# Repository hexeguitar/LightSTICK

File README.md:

# LightStick

![alt text][pic1]

## Features:  
- High CRI >95 dual color white leds (cold/warm).
- Modular system with one Master module and up to 4 secondary modules.
- Linear constant current LED drivers.
- IR remote control (brightness, color, presets).
- Optional analog control using potentiometers (not implemented yet).
- Power saving OFF mode.
- Current consumption: about 300mA per module in full brightness.
  
## Background/design:
Traditional and common studio lights used in photography and filming usually use a high current PWM to control the brightness. For my use in filming analog instruments and effects (often high gain ones) i really needed something quiet and as noise/EMI free as possible.  
That's how the **LightSTICK** modular light was born - it uses linear constant current drivers for the LEDs and a DC control voltage to set the brightness and the color temperature.  
## Modularity
The design is modular, one "Master" module, consisting the MCU and IR receiver can control up to 4 additional secondary modules connected via a 5 wire bus:  
* 12V supply for the LEDs
* 5V supply for the constant current drivers / control voltage reference
* **WH** - cold white control voltage
* **WWH** - warm white control voltage
* GND  
## LED type  
LEDs used in the LightSTICK are manufactured by the LEDGUON company, obtainable through their direct store at Aliexpress.  
The part number is: **JH-5054WWW12S35-T8A-97**
![alt text][pic2]  

## PCB design
PCB is designed as 4 layer one, using the most of the top layer for heat dissipation.  
![alt text][pic3]  
## Firmware
LightSTICK uses ATtiny806 as it's MCU. The firmware is available as Platformio project and compiled with Arduino framework. Only one library is required and included in the /lib folder: **Arduino-IRremote**, which has been modified to support the ATtiny806 chip.  

### Pot support
Initially i planned to use two potentiometers as control input for the brightness and color temp. However, during the firmware development the IR remote control turned out to be much more useful, hence i went that route. Nevertheless, the footprint for pots are provided and a basic interrupt driven ADC read functionality is implemented in case some would need it. Expanding the firmware should not be a hard task.  

### IR remote control
The easiest way to adapt an existing tv/camera remote as LightSTICK controller is to analyze it using a generic arduino board and one of the examples from the **Arduino-IRremote** library (ie. "Receive Demo). Simply write down the protocol of the remote and all the command codes for each button. In my case of a small remote from an old TC card the results were as follows:  
```
Protocol:           RC5

...
+:                  Command=0x3 Toggle=1 Raw-Data=0x19C3
                    Command=0x3 Raw-Data=0x11C3

-:                  Command=0x9 Toggle=1 Raw-Data=0x19C9
                    Command=0x9 Raw-Data=0x11C9

Up:                 Command=0x6 Toggle=1 Raw-Data=0x19C6
                    Command=0x6 Raw-Data=0x11C6
                    
Down:               Command=0xC Toggle=1 Raw-Data=0x19CC
                    Command=0xC Raw-Data=0x11CC

1:                  Command=0xF Toggle=1 Raw-Data=0x19CF
                    Command=0xF Raw-Data=0x11CF

2:                  Command=0x15 Raw-Data=0x11D5
                    Command=0x15 Toggle=1 Raw-Data=0x19D5

3:                  Command=0x10 Toggle=1 Raw-Data=0x19D0
                    Command=0x10 Raw-Data=0x11D0

4:                  Command=0x18 Raw-Data=0x11D8
                    Command=0x18 Toggle=1 Raw-Data=0x19D8

5:                  Command=0x1B Toggle=1 Raw-Data=0x19DB
                    Command=0x1B Raw-Data=0x11DB
...
```
The command codes are then used in the IR command table (*`remote.h`* file)
```c++
/**
 * @brief IR remote command table. 
 * 
 */
typedef enum
{
    CMD_IDLE            = 0x00,
    CMD_PWR_TGL         = 0x39,     // key POWER
    CMD_BRIGHT_INC      = 0x03,     // key +
    CMD_BRIGHT_DEC      = 0x09,     // key -
    CMD_BRIGHT_MAX      = 0x30,     // key PLAY
    CMD_COLOR_WARMER    = 0x06,     // key UP
    CMD_COLOR_COLDER    = 0x0C,     // key DOWN
    CMD_COLOR_WARM      = 0x33,     // key FWD
    CMD_COLOR_COLD      = 0x2D,     // key REW
    CMD_PRESET_0        = 0x27,     // key 0
    CMD_PRESET_1        = 0x0F,     // key 1
    CMD_PRESET_2        = 0x15,     // key 2
    CMD_PRESET_3        = 0x10,     // key 3
    CMD_PRESET_4        = 0x18,     // key 4
    CMD_PRESET_5        = 0x1B,     // key 5
    CMD_PRESET_6        = 0x1E,     // key 6
    CMD_PRESET_7        = 0x11,     // key 7
    CMD_PRESET_8        = 0x21,     // key 8
    CMD_PRESET_9        = 0x12,     // key 9
    CMD_RESET_MCU       = 0x3C,     // key STOP
    CMD_STORE_PRESET    = 0x36      // key REC
}ir_cmd_t;
```  
![alt text][pic5]  
### Low power design  
Both, the electronics and the firmware implements low power design techniques making the LightSTICK useful as battery operated device, too.  
In **OFF** state the global 12V and 5V power busses are disabled, the MCU is in power off state, practically leaving the IR receiver as a single powered on device.

### Programming
ATtiny806 uses UPDI protocol for programming the flash. The programmer should be connected to the pads marked !UPDI, 5V and GND, depending on the used device. Programmers like the Atmel-ICE require the 5V VDD to set the proper logic level.  
An UPDI programmer can be also made of a generic Arduino board. In that case make sure the board runs on 5V, only the UPDI and GND connections will be required.  
The `platformio.ini` file assumes the Atmel-ICE programmer. This file has to be modified if another type of programmer is used.      
First use the following command in Platformio to set the correct fuse values:  
```
pio run -t fuses -e set_fuses
```
and then normally upload the firmware.  

## Applications  
Cheap "book lamp" rebuilt into remote controlled high CRI light for macro photography. Improved thermals by mounting the pcbs on two pieces of 15mm wide alu flat profile with 3mm thick silicon pad isolation.
![alt text][pic6]  
A ring of 5 LightSTICKs used as source of indirect light in macro photography.
![alt text][pic7]  
![alt text][pic4]  

----  
Copyright 2021 by Piotr Zapart  
www.hexefx.com

[pic1]: pics/LighSTICK_a.png "LightSTICK main"
[pic2]: pics/Led_type.jpg "LEDs used in the project"
[pic3]: pics/LightStick9.jpg "LightSTICK"
[pic4]: pics/LightStick8.jpg "LightSTICK"
[pic5]: pics/LightStick6.jpg "LightSTICK"
[pic6]: pics/LightStick11.jpg "LightSTICK"
[pic7]: pics/LightStick12.jpg "LightSTICK"

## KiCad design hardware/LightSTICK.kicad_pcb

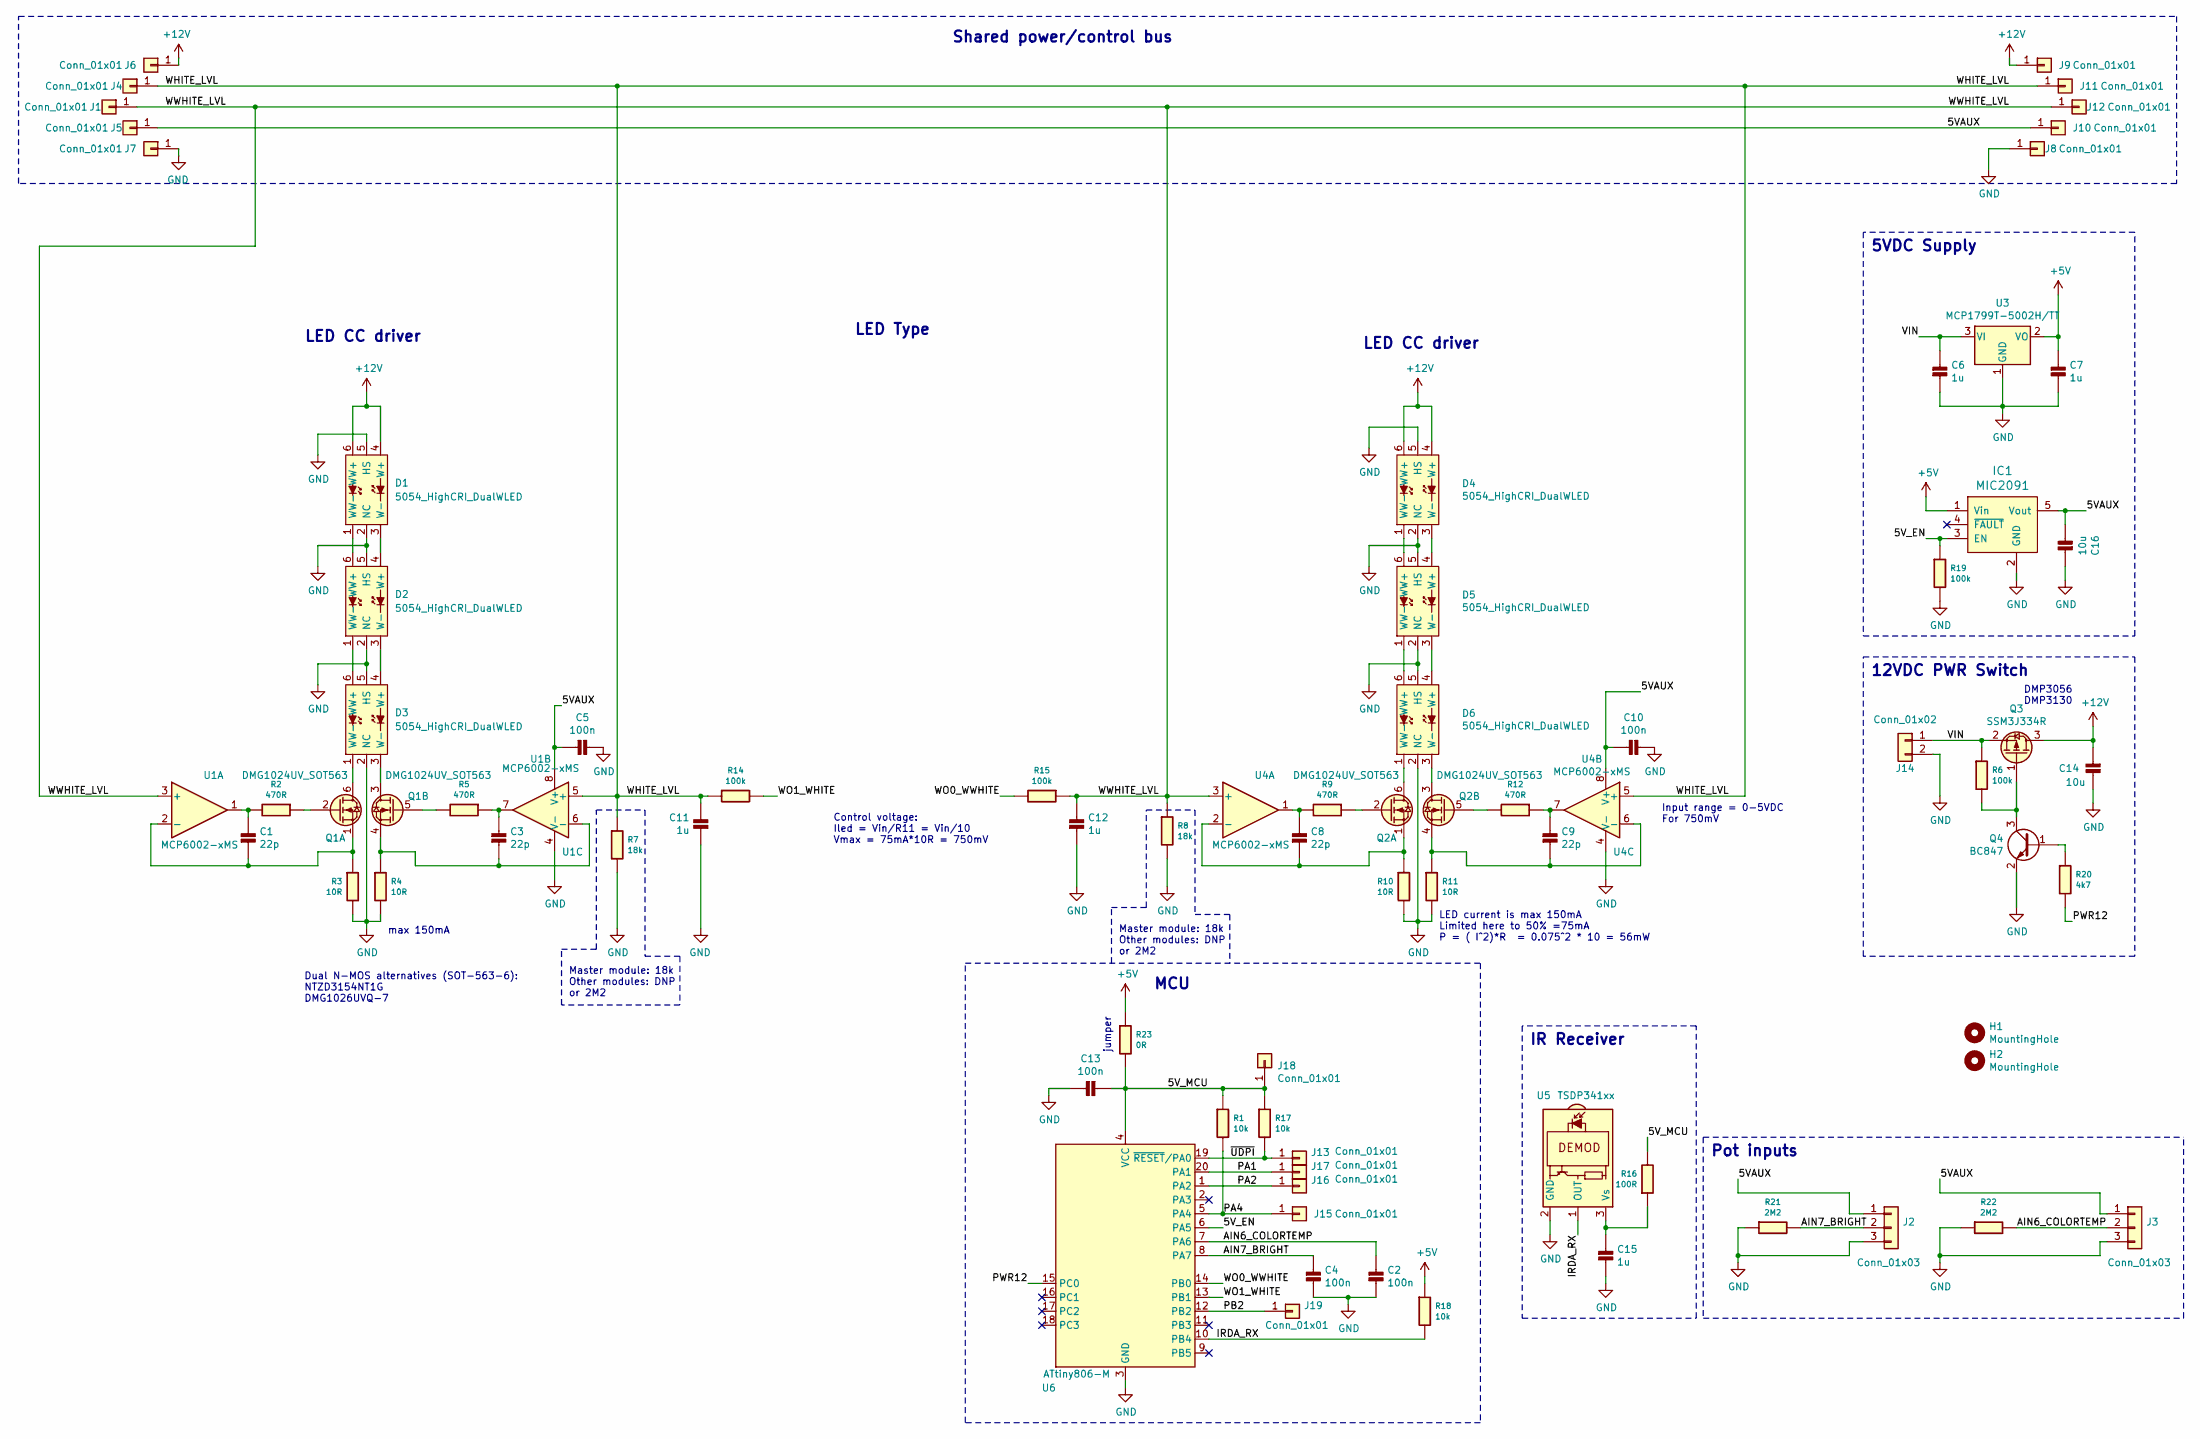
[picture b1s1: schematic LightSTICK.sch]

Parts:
C1, C3, C8, C9: 22p; Hx_C_0603_1608Metric
C2, C4, C5, C10, C13: 100n; Hx_C_0603_1608Metric
C6, C7, C11, C12, C15: 1u; Hx_C_0603_1608Metric
C14: 10u; Hx_C_1206_3216Metric
C16: 10u; Hx_C_0603_1608Metric
D1, D2, D3, D4, D5, D6: 5054_HighCRI_DualWLED; LED_HighCRI_WhiteWarmWhite_5.0x5.0mm_P1.0mm
H1, H2: MountingHole; MountingHole_2.2mm_M2
IC1: MIC2091; SOT-23-5
J1, J4, J5, J6, J7, J8, J9, J10, J11, J12: Conn_01x01; 1x1_1.5x0.8_square
J2, J3: Conn_01x03; PinHeader_1x03_P2.00mm_SMDpads
J13, J15, J16, J17, J18, J19: Conn_01x01; TestPoint_Pad_D1.0mm
J14: Conn_01x02; PinHeader_1x02_P2.54mm_SMDpads
Q1, Q2: DMG1024UV_SOT563; SOT-563
Q3: SSM3J334R; SOT-23
Q4: BC847; SOT-23
R1, R17, R18: 10k; Hx_R_0603_1608Metric
R2, R5, R9, R12: 470R; Hx_R_0603_1608Metric
R3, R4, R10, R11: 10R; Hx_R_0805_2012Metric
R6, R14, R15, R19: 100k; Hx_R_0603_1608Metric
R7, R8: 18k; Hx_R_0603_1608Metric
R16: 100R; Hx_R_0603_1608Metric
R20: 4k7; Hx_R_0603_1608Metric
R21, R22: 2M2; Hx_R_0603_1608Metric
R23: 0R; Hx_R_0805_2012Metric
U1, U4: MCP6002-xMS; SOIC8
U3: MCP1799T-5002H/TT; SOT-23
U5: TSDP341xx; PinHeader_1x03_P2.00mm_SMDpads
U6: ATtiny806-M; VQFN-20-1EP_3x3mm_P0.4mm_EP1.7x1.7mm

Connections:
+5V: C7.1, IC1.1 (Vin), R18.1, R23.1, U3.2 (VO)
+12V: C14.2, D1.4 (W+), D1.6 (WW+), D4.4 (W+), D4.6 (WW+), J6.1, J9.1, Q3.3 (D)
/5VAUX: C5.2, C10.2, C16.2, IC1.5 (Vout), J2.1, J3.1, J5.1, J10.1, U1.8 (V+), U4.8 (V+)
/5V_EN: IC1.3 (EN), R19.1, U6.6 (PA5)
/5V_MCU: C13.2, J18.1, R1.1, R16.2, R17.1, R23.2, U6.4 (VCC)
/AIN6_COLORTEMP: C2.1, J3.2, R22.2, U6.7 (PA6)
/AIN7_BRIGHT: C4.1, J2.2, R21.2, U6.8 (PA7)
/IRDA_RX: R18.2, U5.1 (OUT), U6.10 (PB4)
/PA1: J17.1, U6.20 (PA1)
/PA2: J16.1, U6.1 (PA2)
/PA4: J15.1, R1.2, U6.5 (PA4)
/PB2: J19.1, U6.12 (PB2)
/PWR12: R20.2, U6.15 (PC0)
/VIN: C6.1, J14.1, Q3.2 (S), R6.1, U3.3 (VI)
/WHITE_LVL: C11.1, J4.1, J11.1, R7.1, R14.1, U1.5 (+), U4.5 (+)
/WO0_WWHITE: R15.2, U6.14 (PB0)
/WO1_WHITE: R14.2, U6.13 (PB1)
/WWHITE_LVL: C12.1, J1.1, J12.1, R8.1, R15.1, U1.3 (+), U4.3 (+)
/~UDPI: J13.1, R17.2, U6.19 (~RESET~/PA0)
GND: C2.2, C4.2, C5.1, C6.2, C7.2, C10.1, C11.2, C12.2, C13.1, C14.1, C15.2, C16.1, D1.2 (NC), D1.5 (HS), D2.2 (NC), D2.5 (HS), D3.2 (NC), D3.5 (HS), D4.2 (NC), D4.5 (HS), D5.2 (NC), D5.5 (HS), D6.2 (NC), D6.5 (HS), IC1.2 (GND), J2.3, J3.3, J7.1, J8.1, J14.2, Q4.2 (E), R3.2, R4.2, R7.2, R8.2, R10.2, R11.2, R19.2, R21.1, R22.1, U1.4 (V-), U3.1 (GND), U4.4 (V-), U5.2 (GND), U6.3 (GND), U6.21 (GND)
unnamed: C1.1, R2.2, U1.1
unnamed: C1.2, Q1.1 (S), R3.1, U1.2 (-)
unnamed: C3.1, R5.1, U1.7
unnamed: C3.2, Q1.4 (S), R4.1, U1.6 (-)
unnamed: C8.1, R9.2, U4.1
unnamed: C8.2, Q2.1 (S), R10.1, U4.2 (-)
unnamed: C9.1, R12.1, U4.7
unnamed: C9.2, Q2.4 (S), R11.1, U4.6 (-)
unnamed: C15.1, R16.1, U5.3 (Vs)
unnamed: D1.1 (WW-), D2.6 (WW+)
unnamed: D1.3 (W-), D2.4 (W+)
unnamed: D2.1 (WW-), D3.6 (WW+)
unnamed: D2.3 (W-), D3.4 (W+)
unnamed: D3.1 (WW-), Q1.6 (D)
unnamed: D3.3 (W-), Q1.3 (D)
unnamed: D4.1 (WW-), D5.6 (WW+)
unnamed: D4.3 (W-), D5.4 (W+)
unnamed: D5.1 (WW-), D6.6 (WW+)
unnamed: D5.3 (W-), D6.4 (W+)
unnamed: D6.1 (WW-), Q2.6 (D)
unnamed: D6.3 (W-), Q2.3 (D)
unnamed: Q1.2 (G), R2.1
unnamed: Q1.5 (G), R5.2
unnamed: Q2.2 (G), R9.1
unnamed: Q2.5 (G), R12.2
unnamed: Q3.1 (G), Q4.3 (C), R6.2
unnamed: Q4.1 (B), R20.1

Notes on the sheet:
max 150mA
LED current is max 150mA Limited here to 50% =75mA P = ( I^2)*R = 0.075^2 * 10 = 56mW
Control voltage: Iled = Vin/R11 = Vin/10 Vmax = 75mA*10R = 750mV
Shared power/control bus
LED CC driver
Pot inputs
MCU
5VDC Supply
Input range = 0-5VDC For 750mV
Dual N-MOS alternatives (SOT-563-6): NTZD3154NT1G DMG1026UVQ-7
12VDC PWR Switch
jumper
IR Receiver
DMP3056 DMP3130
Master module: 18k Other modules: DNP or 2M2
LED Type

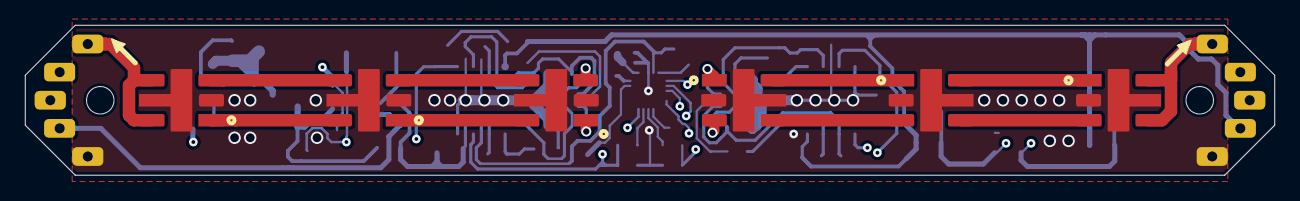
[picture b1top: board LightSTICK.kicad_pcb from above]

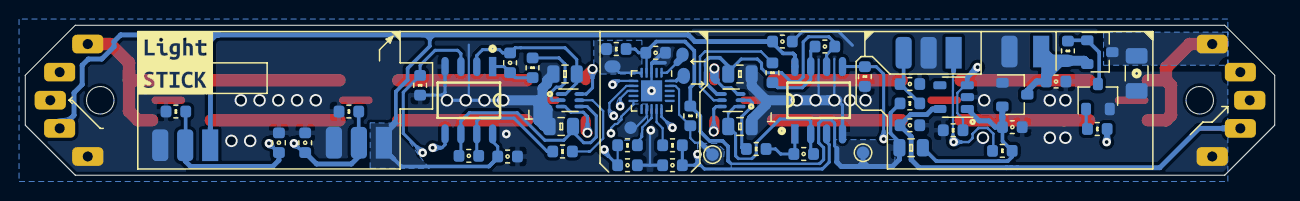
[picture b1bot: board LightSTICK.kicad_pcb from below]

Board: 4 copper layers, 100.0 x 12.0 mm, 76 parts (68 on the bottom side), 47 nets.

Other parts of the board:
svg2mod: G***; label

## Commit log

2021-10-19 fix typos
2021-10-19 readme update
2021-10-20 fix typo

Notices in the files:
hardware/LightSTICK.sch:
(c) 2021 by Piotr Zapart
